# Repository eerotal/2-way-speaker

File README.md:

Two Way Concrete Speakers
-------------------------

This repository contains all design files for my two way concrete speakers
See the PDF file at `latex/documentation.pdf` for the full documentation.
The PDF file is a concatenated version of all of the exported design files.

The contents of this repository are licensed under the CERN OHL v1.2 license
unless otherwise noted. The full license can be found in the file LICENSE.pdf
in the root of this repository.

License
-------

Copyright Eero Talus 2020.

This documentation describes Open Hardware and is licensed under the CERN OHL
v. 1.2.

You may redistribute and modify this documentation under the terms of the
CERN OHL v.1.2. (http://ohwr.org/cernohl). This documentation is distributed
WITHOUT ANY EXPRESS OR IMPLIED WARRANTY, INCLUDING OF MERCHANTABILITY,
SATISFACTORY QUALITY AND FITNESS FOR A PARTICULAR PURPOSE. Please see the
CERN OHL v.1.2 for applicable conditions.

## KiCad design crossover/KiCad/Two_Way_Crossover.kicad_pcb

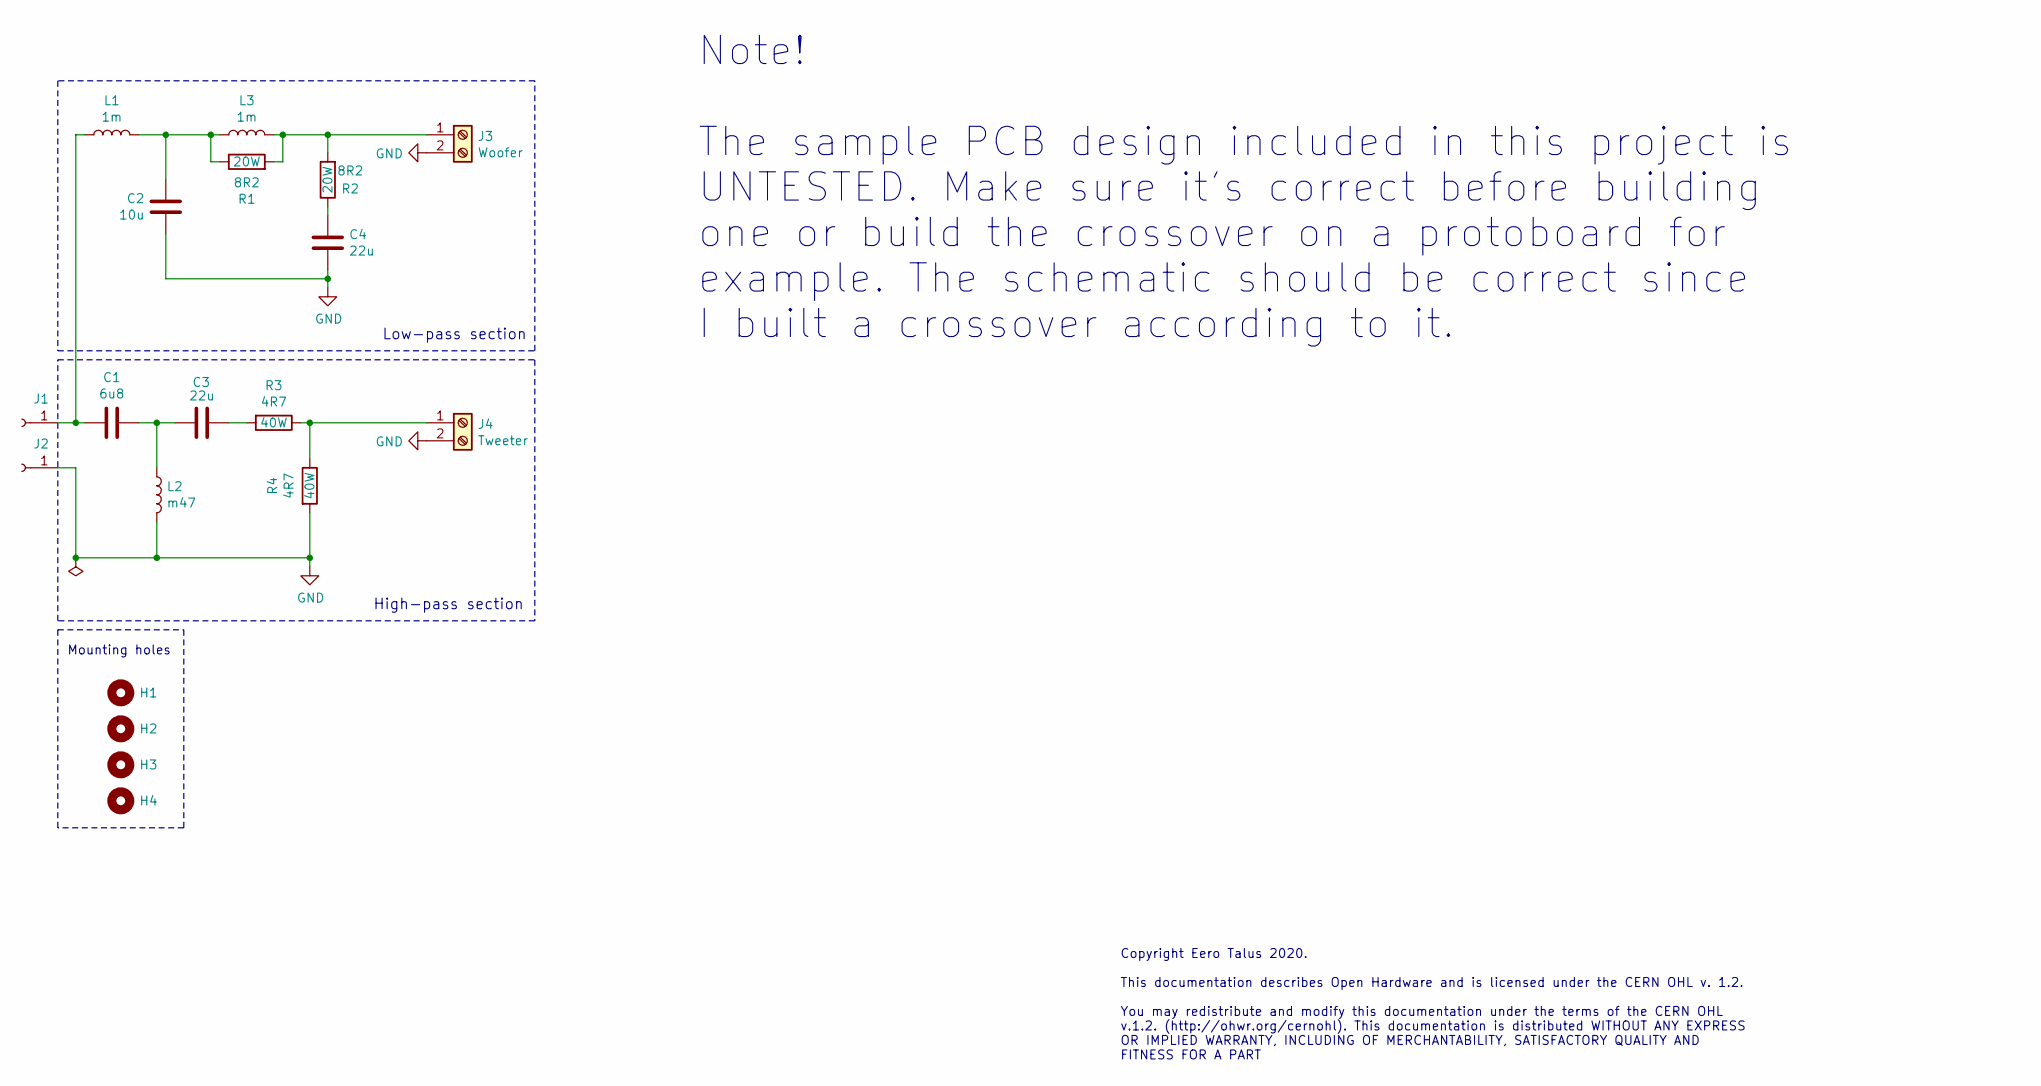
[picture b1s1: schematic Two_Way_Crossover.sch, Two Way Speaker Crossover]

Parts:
C1: 6u8; C_Rect_L31.5mm_W11.0mm_P27.50mm_MKS4
C2: 10u; C_Rect_L26.5mm_W8.5mm_P22.50mm_MKS4
C3, C4: 22u; C_Rect_L31.5mm_W15.0mm_P27.50mm_MKS4
H1, H2, H3, H4: MountingHole; MountingHole_3.2mm_M3_DIN965
J1, J2: Conn_01x01_Female; MountingHole_3.2mm_M3_DIN965_Pad
J3: Woofer; CTBP0508_x2_10.16x8.5x10.20mm_P5.08mm
J4: Tweeter; CTBP0508_x2_10.16x8.5x10.20mm_P5.08mm
L1, L3: 1m; Radial_D36.5mm_H12.0mm_P23.0mm
L2: m47; Radial_D36.5mm_H12.0mm_P23.0mm
R1, R2: 8R2; R_Axial_Power_L60.0mm_W14.0mm_P66.04mm
R3, R4: 4R7; Resistor_Power_Axial_L91.5_W20.2_H20.2

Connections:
GND: C2.1, C4.2, J2.1, J3.2, J4.2, L2.2, R4.2
unnamed: C1.1, C3.1, L2.1
unnamed: C1.2, J1.1, L1.1
unnamed: C2.2, L1.2, L3.1, R1.1
unnamed: C3.2, R3.2
unnamed: C4.1, R2.1
unnamed: J3.1, L3.2, R1.2, R2.2
unnamed: J4.1, R3.1, R4.1

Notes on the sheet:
Mounting holes
Low-pass section
High-pass section
Copyright Eero Talus 2020. This documentation describes Open Hardware and is licensed under the CERN OHL v. 1.2. You may redistribute and modify this documentation under the terms of the CERN OHL v.1.2. (http://ohwr.org/cernohl). This documentation is distributed WITHOUT ANY EXPRESS OR IMPLIED WARR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
Note! The sample PCB design included in this project is UNTESTED. Make sure it's correct before building one or build the crossover on a protoboard for example. The schematic should be correct since I built a crossover according to it.

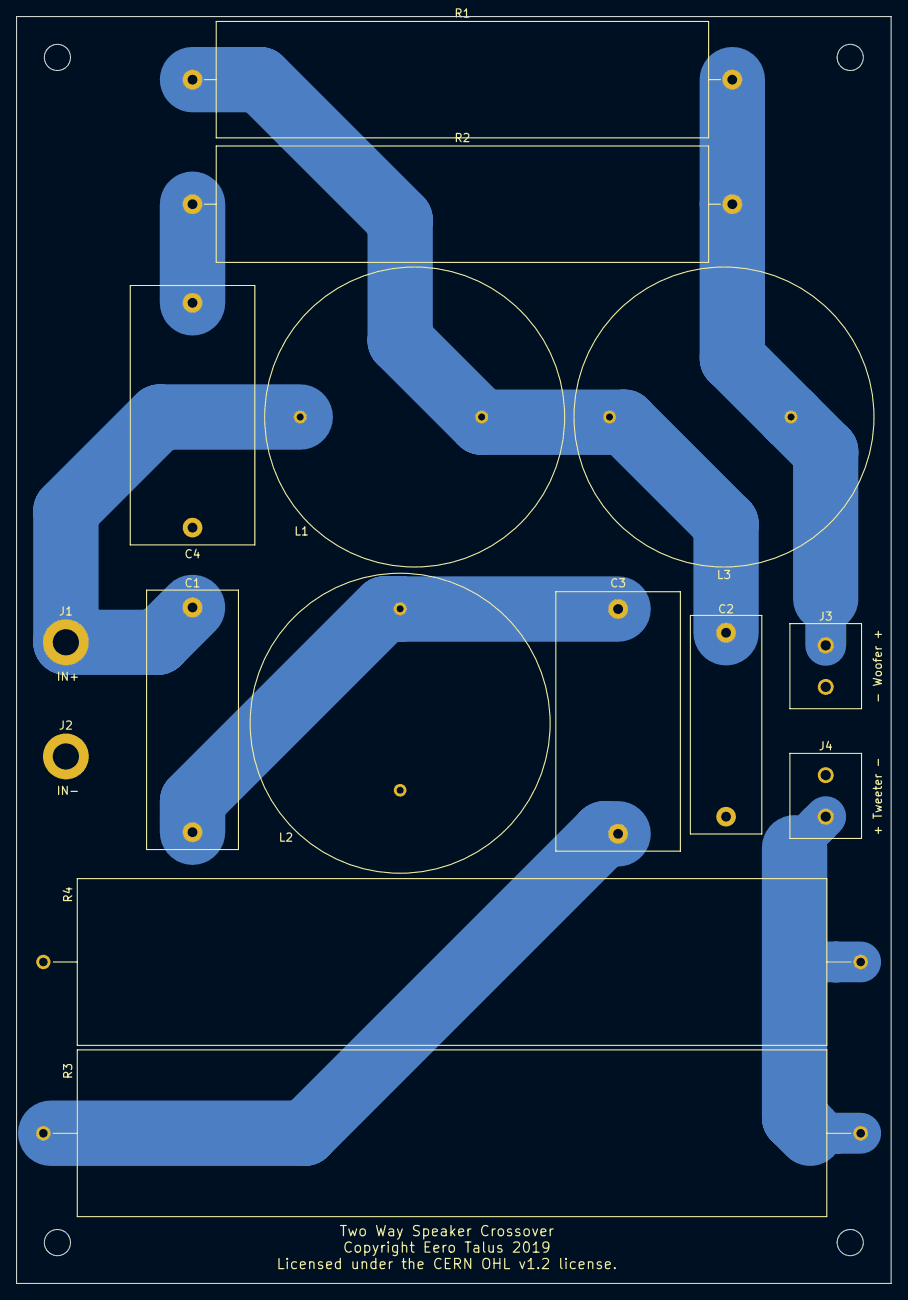
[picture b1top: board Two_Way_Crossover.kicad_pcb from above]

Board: 2 copper layers, 107.0 x 155.0 mm, 19 parts (0 on the bottom side), 8 nets.

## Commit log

2019-07-30 Update notes and add Boxsim simulation
2019-07-30 Model tweeter and cutouts
2019-08-02 Various improvements
2019-08-04 Add threaded inserts
2019-08-05 Fix front panel countersinks
2019-08-05 Improve driver positions
2019-08-05 Model a connector panel
2019-08-05 Improve model, add BOM
2019-08-09 Various tweaks
2019-08-10 Create 2D drawings
2019-08-13 Model a jig for routing the port slot
2019-08-13 Change back and front panel thickness from 20mm to 18mm
2019-08-13 Fix port length + update drawings
2019-09-15 Begin modeling a speaker stand
2019-09-17 Change speaker stand leg angles to 12.5deg
2019-10-06 Change port design
2019-10-14 Tweak port design
2019-10-16 Update simulation & fix drawings
2019-10-16 Fix drawings
2019-11-29 Tweak drawings
2019-11-29 Improve directory layout, generate documentation pdf with sh
2019-11-30 Create proper crossover schematics & PCB + fix ngspice resistor values
2019-11-30 Remove automatically created latex file from repo
2019-12-12 Tweak crossover
2019-12-12 Model a new stand
2019-12-15 Model yet another stand
2019-12-16 Redesign PCB
2019-12-16 Improve stand model
2019-12-18 Create CAM operations for stand plates
2019-12-18 Fix CAM feedrates and spindle speeds
2019-12-19 Partially fix incorrect PCB footprints
2019-12-19 Fix crossover simulation values
2019-12-19 Write better docs
2019-12-31 Modify stand details
2020-01-01 Improve docs
2020-01-01 Add PDFs to repo
2020-01-01 Improve readme
2020-01-01 Tweak stand model CAM settings
2020-01-06 Remove stand model from repo
2020-01-07 Add license
2020-01-07 Rename license file
2020-01-07 Add render to readme
2020-01-07 Add frequency response to docs

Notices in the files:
crossover/KiCad/Two_Way_Crossover.kicad_pcb:
Copyright Eero Talus 2019
